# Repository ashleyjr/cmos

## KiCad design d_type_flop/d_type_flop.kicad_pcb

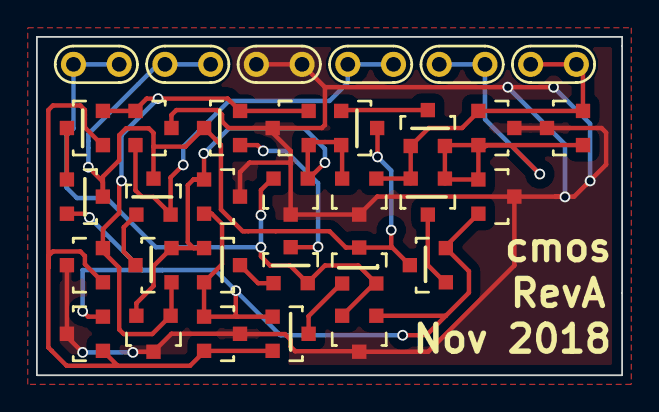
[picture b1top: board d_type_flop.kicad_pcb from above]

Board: 2 copper layers, 32.5 x 18.8 mm, 32 parts (0 on the bottom side), 17 nets.

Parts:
M11, M12, M21, M22, M31, M32, M33, M41, M42, M51, M52, M61, M62: PMOS; SOT-23
M13, M14, M23, M24, M34, M35, M36, M43, M44, M53, M54, M63, M64: NMOS; SOT-23
T1, T2, T3, T4, T5, T6: TEST_1P; Test_Point

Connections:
+3V3: M11.3, M12.3, M21.3, M22.3, M31.3, M32.3, M33.3, M41.3, M42.3, M51.3, M52.3, M61.3, M62.3, T1.1
/1/A: M11.2, M13.2, M33.2, M36.2, M41.1, M42.1, M43.1
/2/A: M11.1, M12.1, M13.1, M21.2, M23.2
/3/A: M12.2, M14.2, M21.1, M22.1, M23.1, M31.2, M34.2, M52.2, M54.2
/4/A: M31.1, M32.1, M33.1, M34.1, M41.2, M43.2, M62.2, M64.2
CLK: M22.2, M24.2, M32.2, M35.2, T3.1
D: M42.2, M44.2, T4.1
GNDREF: M14.3, M24.3, M36.3, M44.3, M54.3, M64.3, T2.1
unnamed: M13.3, M14.1
unnamed: M23.3, M24.1
unnamed: M34.3, M35.1
unnamed: M35.3, M36.1
unnamed: M43.3, M44.1
unnamed: M53.3, M54.1
unnamed: M63.3, M64.1
Q: M51.1, M52.1, M53.1, M61.2, M63.2, T5.1
nQ: M51.2, M53.2, M61.1, M62.1, M63.1, T6.1

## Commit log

2018-01-09 First working inverter sim
2018-01-11 Schematic capture of flop
2018-01-11 Changed model for mos
2018-01-14 Changed sim to ltspice and started hier schematic
2018-01-17 Change d type setup and add NAND3
2018-01-17 first edge sim running
2018-01-20 pwl sim with ltspice
2018-01-21 install wine and ltspice
2018-01-21 Plotting sim with matplotlib
2018-01-21 plot and sim
2018-01-21 Added test points
2018-01-21 Assigned footprint
2018-01-22 Started layout
2018-01-22 more layout
2018-11-10 Relayout headers and flood
2018-11-10 P and N mark, thermal relief
2018-11-10 Export gerbers and adjust floods
2018-12-04 Added bom
